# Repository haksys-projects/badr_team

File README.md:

# badr_team
open source hardware and software projects

<<<<<<< HEAD
1 - ATTINY85 ISP PROGRAMMER SHILED
=======
## Arduino Isp Programmer:
* [instructables](https://www.instructables.com/Yet-Another-ATTINY85-ISP-Programmer-Shield-for-Ard/)
* [haksys](http://www.haksys.fr/yet-another-attiny85-isp-programmer-shield-for-arduino/)
>>>>>>> dc44b8407c87f34ecd592266d91b0a22ada67b9a

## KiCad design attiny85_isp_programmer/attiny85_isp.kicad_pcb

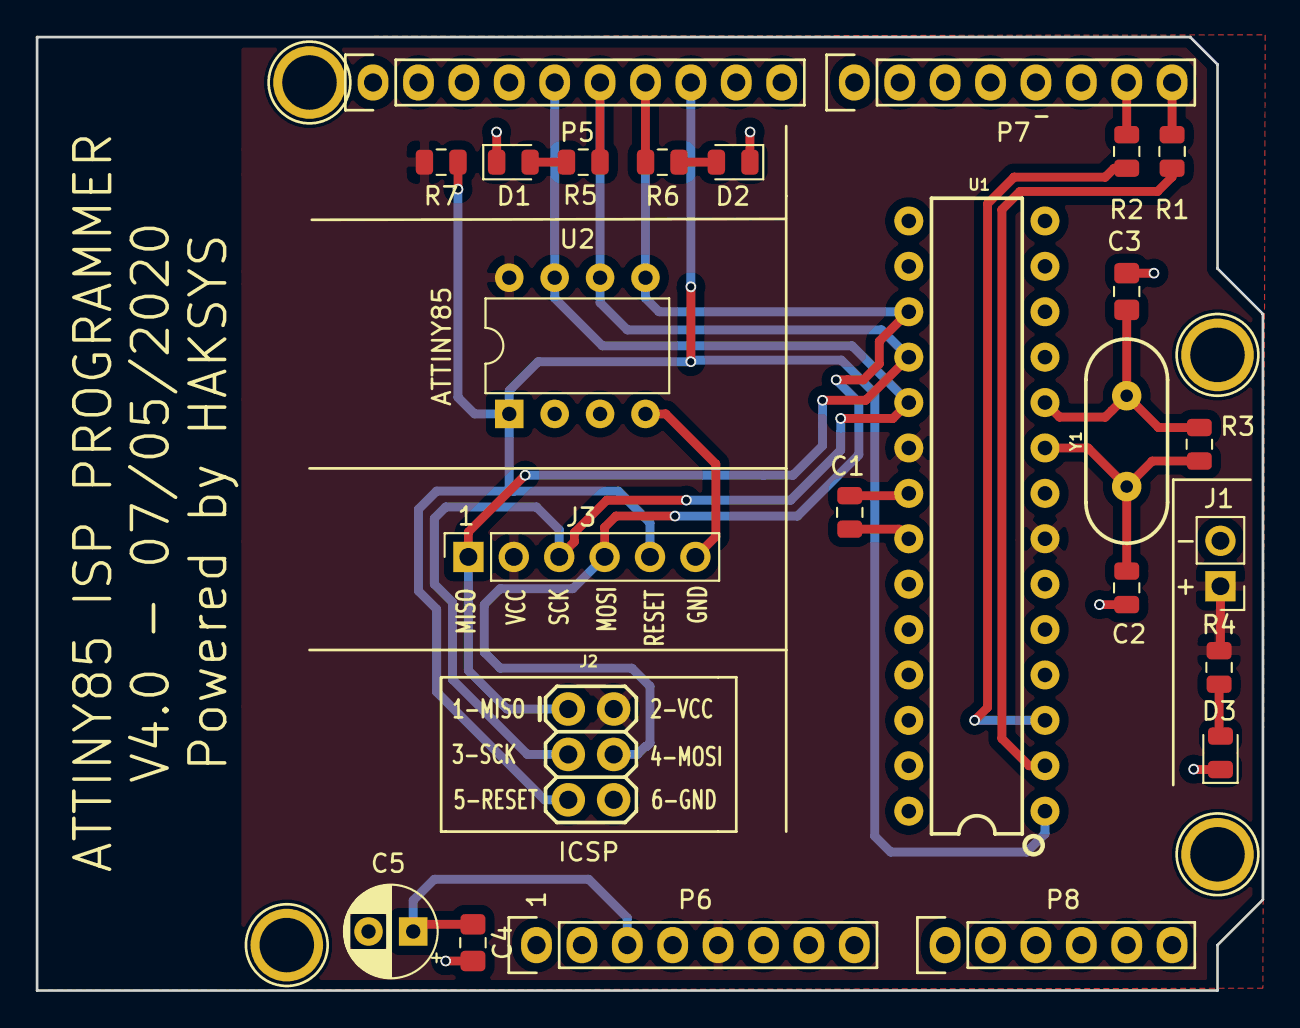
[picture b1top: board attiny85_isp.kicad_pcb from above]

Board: 2 copper layers, 68.6 x 53.3 mm, 29 parts (0 on the bottom side), 19 nets.

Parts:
C1: 0.1uF; C_0805_2012Metric
C2: 27pF; C_0805_2012Metric
C3: 27pF; C_0805_2012Metric_Pad1.15x1.40mm_HandSolder
C4: 10uF; C_0805_2012Metric_Pad1.15x1.40mm_HandSolder
C5: 10uF; CP_Radial_D5.0mm_P2.50mm
D1, D2: BLUE; LED_0805_2012Metric
D3: RED; LED_0805_2012Metric
J1: Conn_01x02_Male; PinHeader_1x02_P2.54mm_Vertical
J2: CONN_03X2FEMALE; 2X3
J3: Conn_01x06_Female; PinSocket_1x06_P2.54mm_Vertical
P1, P2, P3, P4: CONN_01X01; Arduino_1pin
P5: Digital; Socket_Strip_Arduino_1x10
P6: Power; Socket_Strip_Arduino_1x08
P7: Digital; Socket_Strip_Arduino_1x08
P8: Analog; Socket_Strip_Arduino_1x06
R1, R2, R4, R5, R6: 1K; R_0805_2012Metric
R3: 1M; R_0805_2012Metric
R7: 10K; R_0805_2012Metric
U1: ATMEGA328P_PDIP; DIP28
U2: ATtiny85-20PU; DIP-8_W7.62mm
Y1: 16MHZ; HC49US

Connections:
0(Rx): P7.8, R1.1
1(Tx): P7.7, R2.1
10(SS): J2.5, J3.5, P5.8, R7.1, U1.1, U2.1
11(MOSI): J2.4, J3.4, P5.7, R6.2, U1.17, U2.5
12(MISO): J2.1, J3.1, P5.6, R5.2, U1.18, U2.6
13(SCK): J2.3, J3.3, P5.5, U1.19, U2.7
+5V: J1.1, J2.2, J3.2, P6.5, R4.2, R7.2, U1.7, U1.20, U2.8
/A4(SDA): P5.2, P8.5
/A5(SCL): P5.1, P8.6
GND: C1.2, C2.1, C3.2, C4.2, C5.2, D1.1, D2.1, D3.1, J1.2, J2.6, J3.6, P5.4, P6.6, P6.7, U1.8, U1.22, U2.4
unnamed: C1.1, U1.21
unnamed: C2.2, R3.1, U1.9, Y1.1
unnamed: C3.1, R3.2, U1.10, Y1.2
unnamed: D1.2, R5.1
unnamed: D2.2, R6.1
unnamed: D3.2, R4.1
unnamed: R1.2, U1.2
unnamed: R2.2, U1.3
Reset: C4.1, C5.1, P6.3

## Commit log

2020-11-23 add the arduino isp programmer project
2020-11-23 Update README.md
    Add "Arduino Isp Programmer" user guide documentation.
2020-11-26 adds licence & readme file plus renaming the repo
2020-11-26 Update readme file
